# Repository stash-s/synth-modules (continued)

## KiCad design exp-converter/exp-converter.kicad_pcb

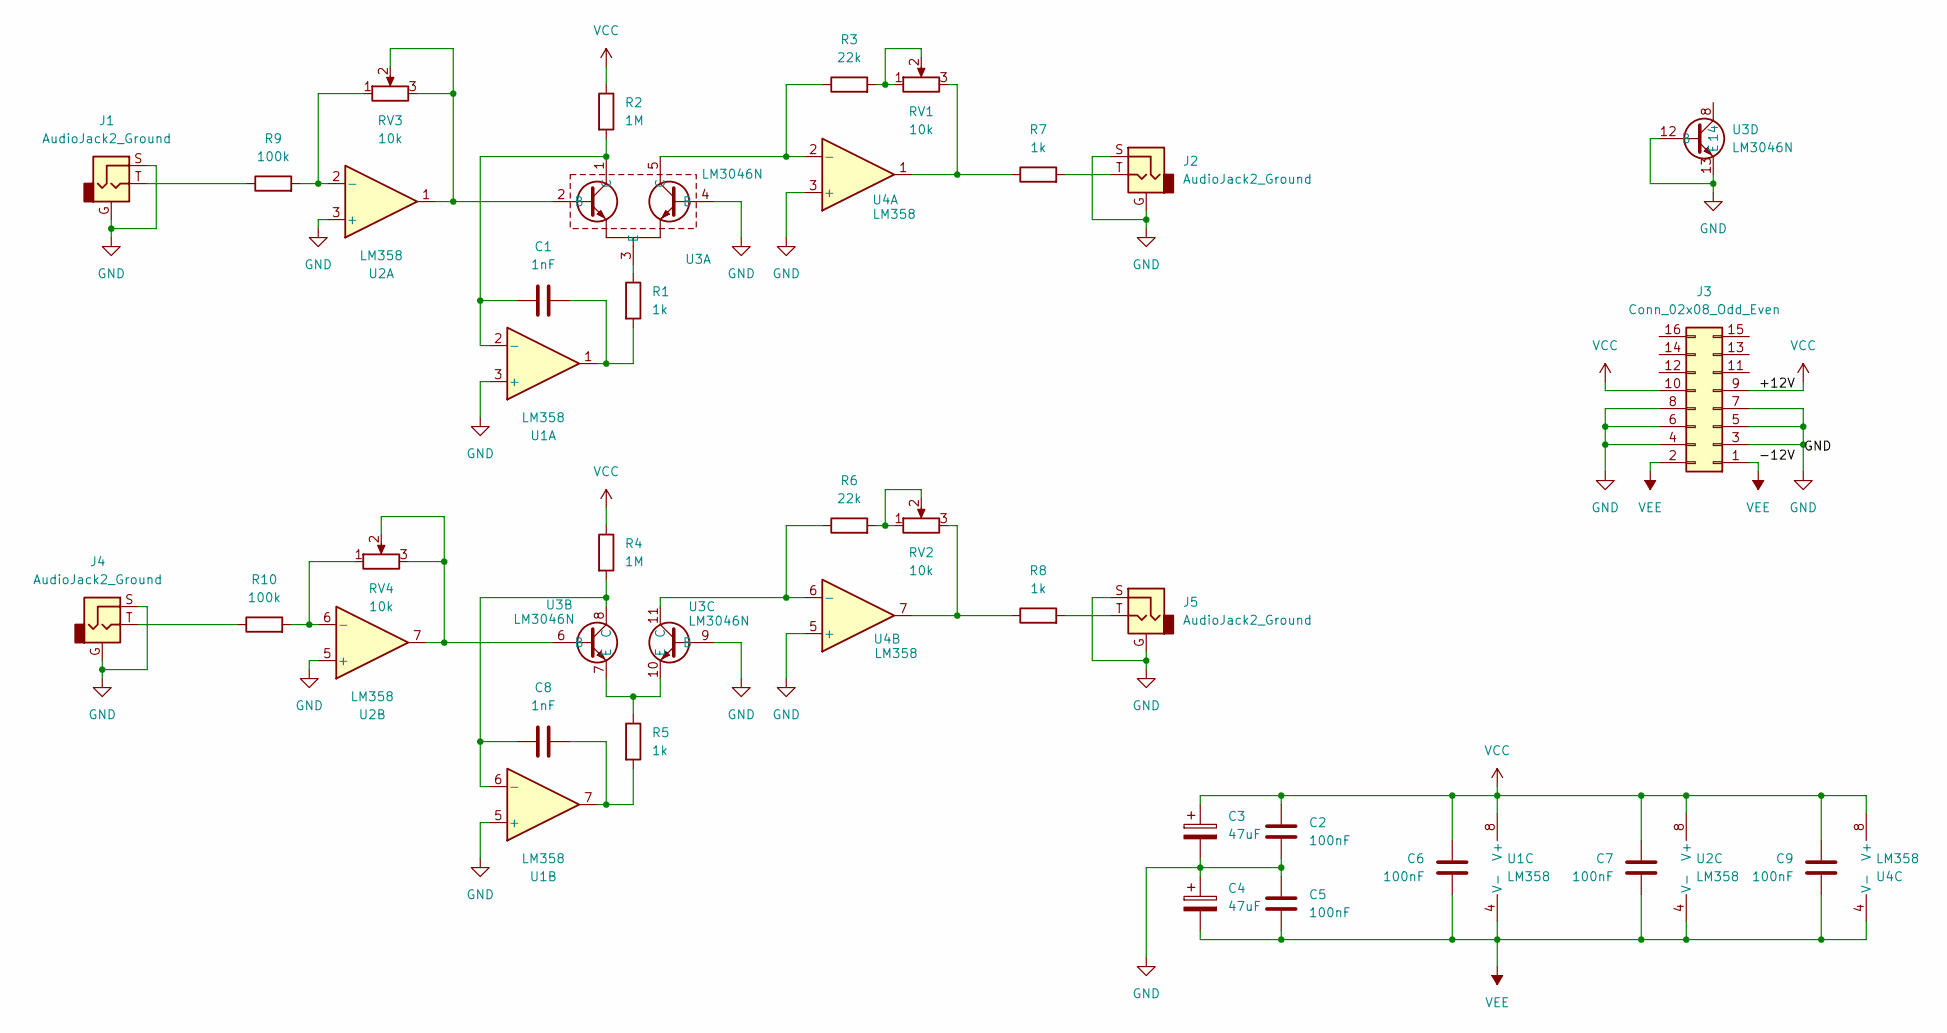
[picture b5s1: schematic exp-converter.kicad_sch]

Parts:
C1, C8: 1nF; C_Disc_D5.0mm_W2.5mm_P5.00mm
C2, C5, C6, C7, C9: 100nF; C_Disc_D5.0mm_W2.5mm_P5.00mm
C3, C4: 47uF; CP_Radial_D8.0mm_P2.50mm
J1, J2, J4, J5: AudioJack2_Ground; Jack_3.5mm_PJ-341-2_Vertical
J3: Conn_02x08_Odd_Even; IDC-Header_2x08_P2.54mm_Vertical
R1, R5, R7, R8: 1k; R_Axial_DIN0207_L6.3mm_D2.5mm_P7.62mm_Horizontal
R2, R4: 1M; R_Axial_DIN0207_L6.3mm_D2.5mm_P7.62mm_Horizontal
R3, R6: 22k; R_Axial_DIN0207_L6.3mm_D2.5mm_P7.62mm_Horizontal
R9, R10: 100k; R_Axial_DIN0207_L6.3mm_D2.5mm_P7.62mm_Horizontal
RV1, RV2, RV3, RV4: 10k; Potentiometer_Runtron_RM-065_Vertical
U1, U2, U4: LM358; DIP-8_W7.62mm_Socket
U3: LM3046N; DIP-14_W7.62mm_Socket

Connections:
GND: C2.2, C3.2, C4.1, C5.1, J1.G, J1.S, J2.G, J2.S, J3.3, J3.4, J3.5, J3.6, J3.7, J3.8, J4.G, J4.S, J5.G, J5.S, U1.3 (+), U1.5 (+), U2.3 (+), U2.5 (+), U3.4 (B), U3.9 (B), U3.12 (B), U3.13 (E), U4.3 (+), U4.5 (+)
unnamed: C1.1, R1.2, U1.1
unnamed: C8.1, R5.2, U1.7
unnamed: J1.T, R9.1
unnamed: J2.T, R7.2
unnamed: J4.T, R10.1
unnamed: J5.T, R8.2
unnamed: R3.2, RV1.1, RV1.2
unnamed: R6.2, RV2.1, RV2.2
unnamed: R7.1, RV1.3, U4.1
unnamed: R8.1, RV2.3, U4.7
unnamed: RV3.2, RV3.3, U2.1, U3.2 (B)
unnamed: C1.2, R2.2, U1.2 (-), U3.1 (C)
unnamed: C8.2, R4.2, U1.6 (-), U3.8 (C)
unnamed: R9.2, RV3.1, U2.2 (-)
unnamed: R10.2, RV4.1, U2.6 (-)
unnamed: R1.1, U3.3 (E)
unnamed: RV4.2, RV4.3, U2.7, U3.6 (B)
unnamed: R5.1, U3.7 (E), U3.10 (E)
unnamed: R6.1, U3.11 (C), U4.6 (-)
unnamed: R3.1, U3.5 (C), U4.2 (-)
VCC: C2.1, C3.1, C6.1, C7.1, C9.1, J3.9, J3.10, R2.1, R4.1, U1.8 (V+), U2.8 (V+), U4.8 (V+)
VEE: C4.2, C5.2, C6.2, C7.2, C9.2, J3.1, J3.2, U1.4 (V-), U2.4 (V-), U4.4 (V-)

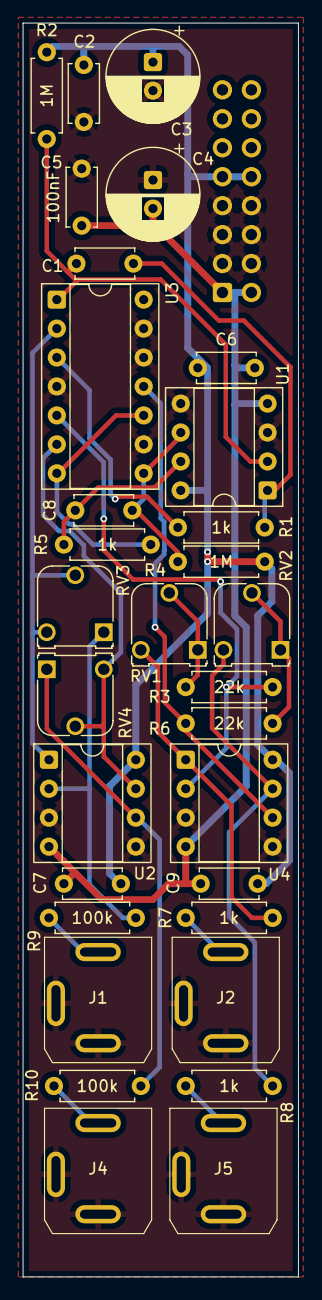
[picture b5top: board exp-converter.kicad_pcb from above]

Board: 2 copper layers, 24.2 x 110.0 mm, 32 parts (1 on the bottom side), 23 nets.

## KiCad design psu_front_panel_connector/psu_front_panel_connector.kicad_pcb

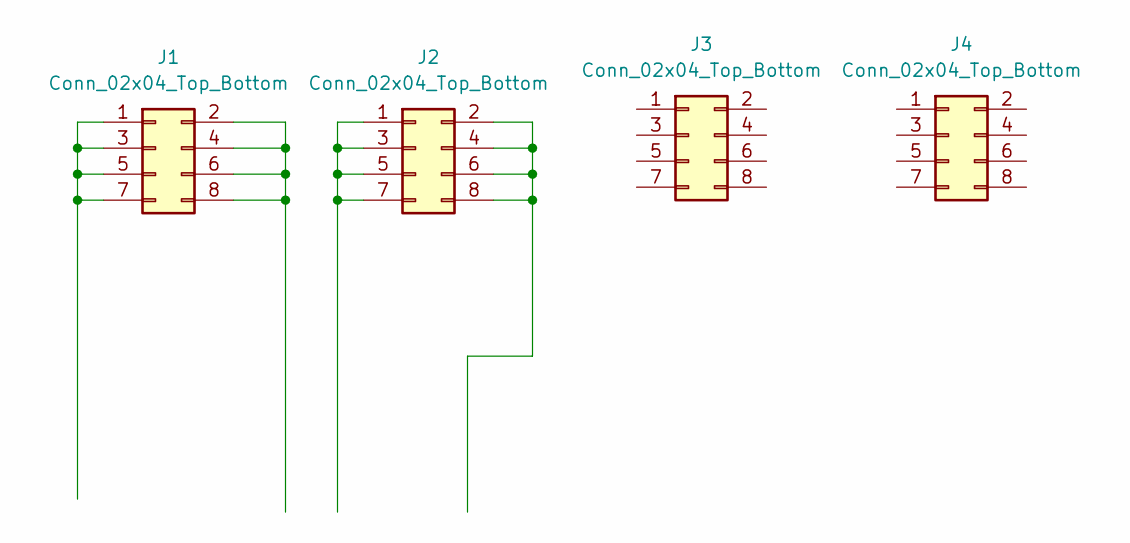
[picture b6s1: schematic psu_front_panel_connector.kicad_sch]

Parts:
J1, J2, J3, J4: Conn_02x04_Top_Bottom; PinSocket_2x04_P2.54mm_Vertical

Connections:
unnamed: J1.1, J1.3, J1.5, J1.7
unnamed: J1.2, J1.4, J1.6, J1.8
unnamed: J2.1, J2.3, J2.5, J2.7
unnamed: J2.2, J2.4, J2.6, J2.8

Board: 2 copper layers, 4 parts (0 on the bottom side), 4 nets, no tracks yet.

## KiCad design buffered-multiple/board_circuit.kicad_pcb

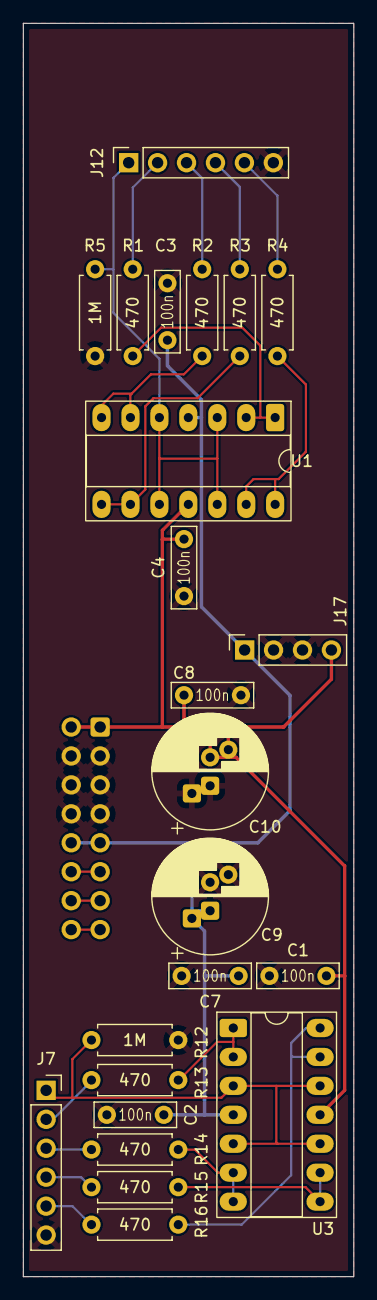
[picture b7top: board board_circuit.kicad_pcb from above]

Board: 2 copper layers, 29.0 x 110.0 mm, 25 parts (1 on the bottom side), 24 nets.

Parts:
C1, C2, C3, C4, C7, C8: 100n; C_Rect_L7.0mm_W2.0mm_P5.00mm
C9, C10: 47uF; CP_Radial_D10.0mm_P2.50mm_P5.00mm
Circuit: Board
J7, J12: Conn_01x06_Socket; PinSocket_1x06_P2.54mm_Vertical
J15: Conn_02x08_Odd_Even; IDC-Header_2x08_P2.54mm_Vertical
J17: Conn_01x04_Socket; PinSocket_1x04_P2.54mm_Vertical
R1, R2, R3, R4, R13, R14, R15, R16: 470; R_Axial_DIN0207_L6.3mm_D2.5mm_P7.62mm_Horizontal
R5, R12: 1M; R_Axial_DIN0207_L6.3mm_D2.5mm_P7.62mm_Horizontal
U1, U3: TL074; DIP-14_W7.62mm_Socket_LongPads

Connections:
+12V_2: C2.1, C3.1, C7.1, C9.1, J15.9, J15.10, J17.1, U1.4 (V+), U3.4 (V+)
-12V_2: C1.2, C4.2, C8.2, C10.2, J15.1, J15.2, J17.4, U1.11 (V-), U3.11 (V-)
GND2: C1.1, C2.2, C3.2, C4.1, C7.2, C8.1, C9.2, C10.1, J7.6, J12.6, J15.3, J15.4, J15.5, J15.6, J15.7, J15.8, J17.2, J17.3, R5.1, R12.1
IN_2A: J12.1, R5.2, U1.3 (+), U1.5 (+), U1.10 (+), U1.12 (+)
IN_2B: J7.1, R12.2, U3.3 (+), U3.5 (+), U3.10 (+), U3.12 (+)
unnamed: J7.2, R13.2
unnamed: J7.3, R14.2
unnamed: J7.4, R15.2
unnamed: J7.5, R16.2
unnamed: J12.2, R1.2
unnamed: J12.3, R2.2
unnamed: J12.4, R3.2
unnamed: J12.5, R4.2
unnamed: J15.11, J15.12
unnamed: J15.13, J15.14
unnamed: J15.15, J15.16
unnamed: R1.1, U1.1, U1.2 (-)
unnamed: R2.1, U1.6 (-), U1.7
unnamed: R3.1, U1.8, U1.9 (-)
unnamed: R4.1, U1.13 (-), U1.14
unnamed: R13.1, U3.1, U3.2 (-)
unnamed: R14.1, U3.6 (-), U3.7
unnamed: R15.1, U3.8, U3.9 (-)
unnamed: R16.1, U3.13 (-), U3.14

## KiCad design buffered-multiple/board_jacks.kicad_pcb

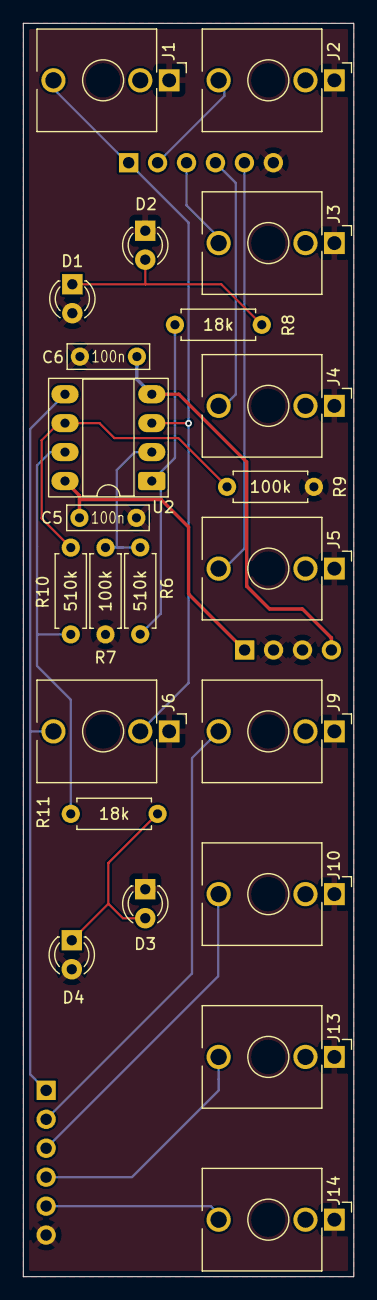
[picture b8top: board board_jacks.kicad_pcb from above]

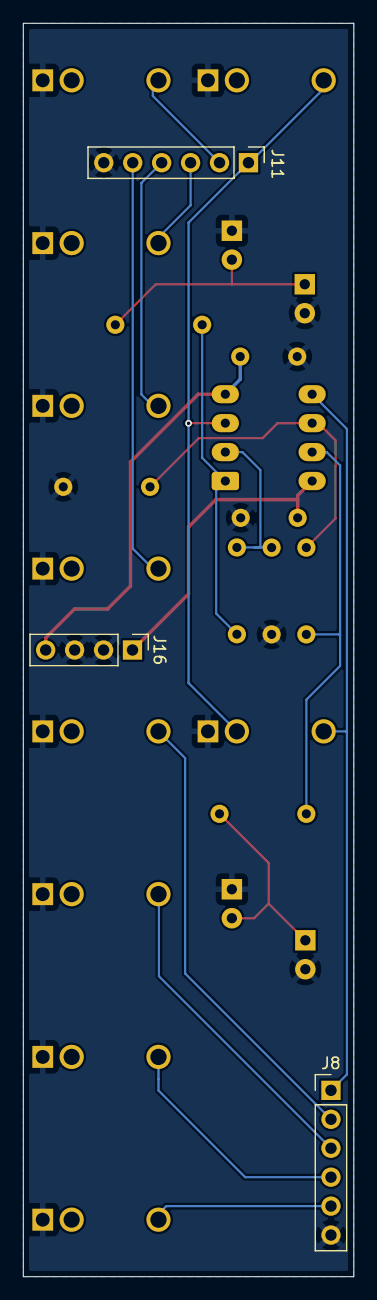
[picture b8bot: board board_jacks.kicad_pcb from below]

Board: 2 copper layers, 29.0 x 110.0 mm, 27 parts (3 on the bottom side), 19 nets.

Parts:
C5, C6: 100n; C_Rect_L7.0mm_W2.0mm_P5.00mm
D1, D2, D3, D4: LED; LED_D3.0mm
J1, J2, J3, J4, J5, J6, J9, J10, J13, J14: AudioJack_Switch; Jack_3.5mm_Switch
J8, J11: Conn_01x06_Pin; PinHeader_1x06_P2.54mm_Vertical
J16: Conn_01x04_Pin; PinHeader_1x04_P2.54mm_Vertical
Jacks: Board
R6, R10: 510k; R_Axial_DIN0207_L6.3mm_D2.5mm_P7.62mm_Horizontal
R7, R9: 100k; R_Axial_DIN0207_L6.3mm_D2.5mm_P7.62mm_Horizontal
R8, R11: 18k; R_Axial_DIN0207_L6.3mm_D2.5mm_P7.62mm_Horizontal
U2: TL072; DIP-8_W7.62mm_Socket_LongPads

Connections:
+12V_1: C5.1, J16.1, U2.8 (V+)
-12V_1: C6.2, J16.4, U2.4 (V-)
GND1: C5.2, C6.1, D1.2 (A), D2.1 (K), D3.1 (K), D4.2 (A), J1.S, J2.S, J3.S, J4.S, J5.S, J6.S, J8.6, J9.S, J10.S, J11.6, J13.S, J14.S, J16.2, J16.3, R7.1, R9.1
IN_1A: J1.T, J6.TN, J11.1, U2.3 (+)
IN_1B: J6.T, J8.1, U2.5 (+)
unnamed: D1.1 (K), D2.2 (A), R8.2
unnamed: D3.2 (A), D4.1 (K), R11.2
unnamed: J8.2, J9.T
unnamed: J8.3, J10.T
unnamed: J8.4, J13.T
unnamed: J8.5, J14.T
unnamed: J2.T, J11.2
unnamed: J3.T, J11.3
unnamed: J4.T, J11.4
unnamed: J5.T, J11.5
unnamed: R6.2, R8.1, U2.1
unnamed: R10.2, R11.1, U2.7
unnamed: R6.1, R7.2, U2.2 (-)
unnamed: R9.2, R10.1, U2.6 (-)

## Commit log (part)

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2025-11-12 Power Rail PCB
2025-11-14 First version of VCA
2025-11-14 Version sent to jlcpcb
2025-11-14 Removed large unneeded file
2025-11-17 Added exponetial converter board
2025-11-18 Exp. converter parts placed
2025-11-20 Nearly finished exp converter PCB.
2025-11-21 Exp converter simmulation works
2025-11-29 Fix potentiometers footprint.
2025-11-29 added PSU front panel connector
2025-11-29 Cleaned up footprints
2025-12-04 Linear VCA mismatched TL072 power supply fixed.
2025-12-05 Fixed OpAmp power rails.
2025-12-05 Added simulations
2025-12-29 Added panel generate script
2025-12-29 VCA v. 2.0
2026-01-13 Updated VCA-1 panel
2026-01-16 Added limiter
2026-02-07 Front panel and output gain fix.
2026-02-07 Simulated exponential VCA control stage
2026-02-08 Exponential VCA PCB ready.
2026-02-22 E24 series components selected for 0-5V VC and ~<500 uA output.
2026-04-02 Exponential VCA ver. 1.2
2026-05-17 Fixed buffered multiple reversed polarity problem.
2026-05-17 Added vu meter simmulation and SOT-23-THIN package.
